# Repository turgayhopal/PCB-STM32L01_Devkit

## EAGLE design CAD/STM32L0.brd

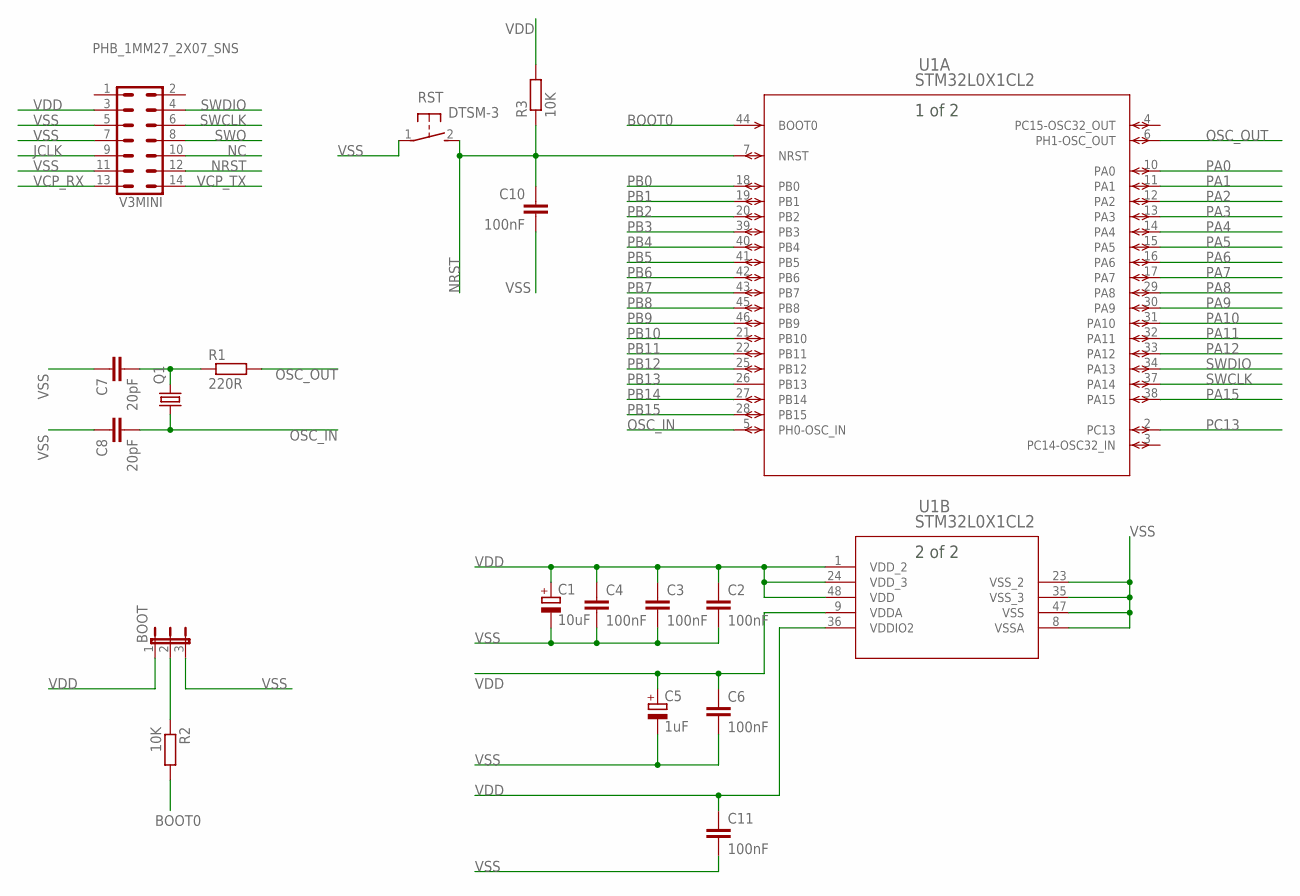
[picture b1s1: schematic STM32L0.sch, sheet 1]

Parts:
BOOT: JP2E; JP2
C1: 10uF; SMC_A
C2, C3, C4, C6, C10, C11: 100nF; C0805
C5: 1uF; SMC_A
C7, C8: 20pF; C0805
Q1: CRYSTALSM49; SM49
R1: 220R; R0805
R2, R3: 10K; R0805
RST: DTSM-3
U1: STM32L0X1CL2; LQFP48-7X7MM
V3MINI: PHB_1MM27_2X07_SNS

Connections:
BOOT0: R2.2, U1.44 (BOOT0)
JCLK: V3MINI.9
unnamed: C7.2, Q1.2, R1.1
unnamed: BOOT.2, R2.1
NC: V3MINI.10
NRST: C10.1, R3.1, RST.2, U1.7 (NRST), V3MINI.12
OSC_IN: C8.2, Q1.1, U1.5 (PH0-OSC_IN)
OSC_OUT: R1.2, U1.6 (PH1-OSC_OUT)
PA0: U1.10 (PA0); also elsewhere on the board
PA1: U1.11 (PA1); also elsewhere on the board
PA2: U1.12 (PA2); also elsewhere on the board
PA3: U1.13 (PA3); also elsewhere on the board
PA4: U1.14 (PA4); also elsewhere on the board
PA5: U1.15 (PA5); also elsewhere on the board
PA6: U1.16 (PA6); also elsewhere on the board
PA7: U1.17 (PA7); also elsewhere on the board
PA8: U1.29 (PA8); also elsewhere on the board
PA9: U1.30 (PA9); also elsewhere on the board
PA10: U1.31 (PA10); also elsewhere on the board
PA11: U1.32 (PA11); also elsewhere on the board
PA12: U1.33 (PA12); also elsewhere on the board
PA15: U1.38 (PA15); also elsewhere on the board
PB0: U1.18 (PB0); also elsewhere on the board
PB1: U1.19 (PB1); also elsewhere on the board
PB2: U1.20 (PB2); also elsewhere on the board
PB3: U1.39 (PB3); also elsewhere on the board
PB4: U1.40 (PB4); also elsewhere on the board
PB5: U1.41 (PB5); also elsewhere on the board
PB6: U1.42 (PB6); also elsewhere on the board
PB7: U1.43 (PB7); also elsewhere on the board
PB8: U1.45 (PB8); also elsewhere on the board
PB9: U1.46 (PB9); also elsewhere on the board
PB10: U1.21 (PB10); also elsewhere on the board
PB11: U1.22 (PB11); also elsewhere on the board
PB12: U1.25 (PB12); also elsewhere on the board
PB13: U1.26 (PB13); also elsewhere on the board
PB14: U1.27 (PB14); also elsewhere on the board
PB15: U1.28 (PB15); also elsewhere on the board
PC13: U1.2 (PC13); also elsewhere on the board
SWCLK: U1.37 (PA14), V3MINI.6
SWDIO: U1.34 (PA13), V3MINI.4
SWO: V3MINI.8
VCP_RX: V3MINI.13
VCP_TX: V3MINI.14
VDD: BOOT.1, C1.+, C2.1, C3.1, C4.1, C5.+, C6.1, C11.1, R3.2, U1.1 (VDD_2), U1.9 (VDDA), U1.24 (VDD_3), U1.36 (VDDIO2), U1.48 (VDD), V3MINI.3; also elsewhere on the board
VSS: BOOT.3, C1.-, C2.2, C3.2, C4.2, C5.-, C6.2, C7.1, C8.1, C10.2, C11.2, RST.1, U1.8 (VSSA), U1.23 (VSS_2), U1.35 (VSS_3), U1.47 (VSS), V3MINI.5, V3MINI.7, V3MINI.11; also elsewhere on the board

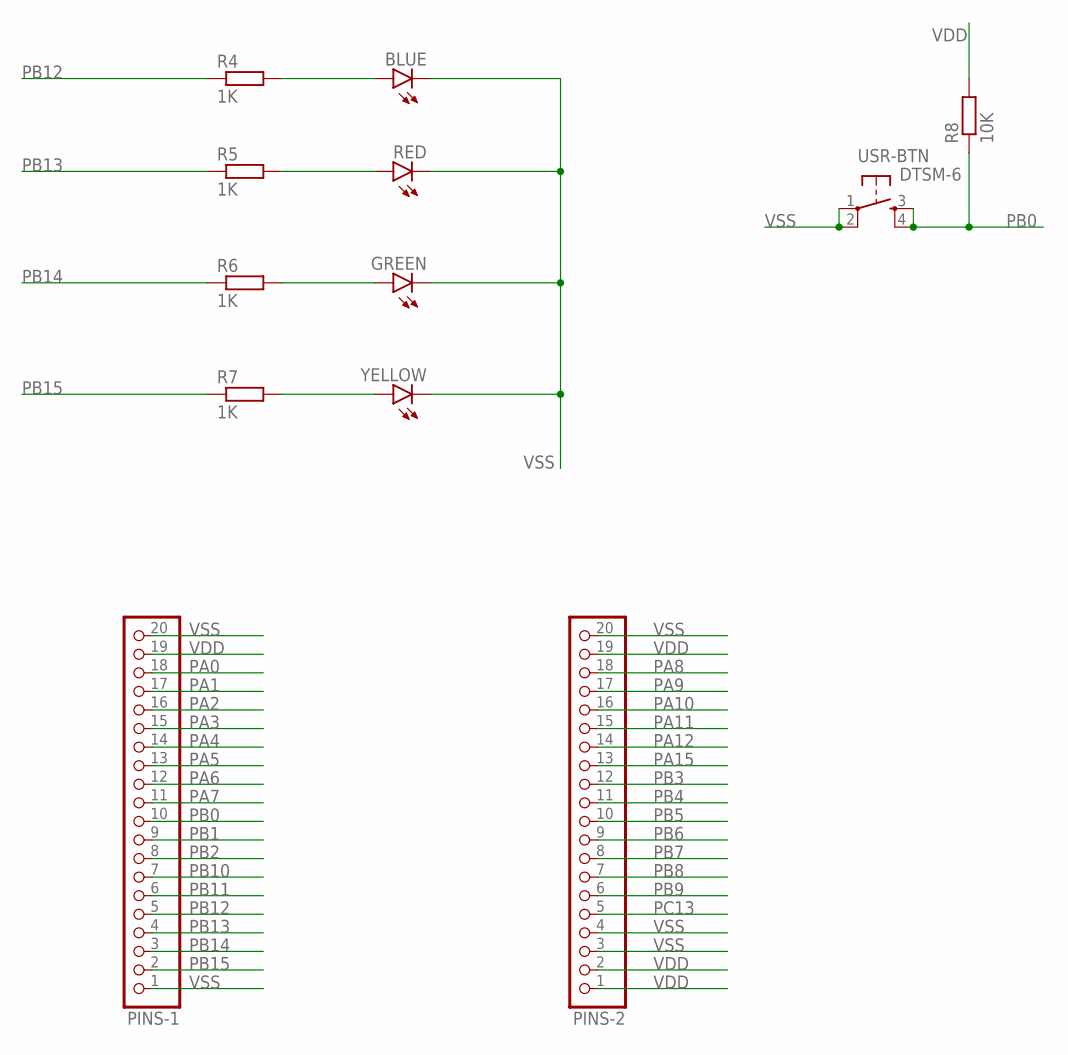
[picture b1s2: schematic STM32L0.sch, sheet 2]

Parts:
BLUE: LEDCHIPLED_0805; CHIPLED_0805
GREEN: LEDCHIPLED_0805; CHIPLED_0805
PINS-1, PINS-2: PINHD-1X20; 1X20
R4, R5, R6, R7: 1K; R0805
R8: 10K; R0805
RED: LEDCHIPLED_0805; CHIPLED_0805
USR-BTN: DTSM-6
YELLOW: LEDCHIPLED_0805; CHIPLED_0805

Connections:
unnamed: BLUE.A, R4.2
unnamed: R5.2, RED.A
unnamed: GREEN.A, R6.2
unnamed: R7.2, YELLOW.A
PA0: PINS-1.18; also elsewhere on the board
PA1: PINS-1.17; also elsewhere on the board
PA2: PINS-1.16; also elsewhere on the board
PA3: PINS-1.15; also elsewhere on the board
PA4: PINS-1.14; also elsewhere on the board
PA5: PINS-1.13; also elsewhere on the board
PA6: PINS-1.12; also elsewhere on the board
PA7: PINS-1.11; also elsewhere on the board
PA8: PINS-2.18; also elsewhere on the board
PA9: PINS-2.17; also elsewhere on the board
PA10: PINS-2.16; also elsewhere on the board
PA11: PINS-2.15; also elsewhere on the board
PA12: PINS-2.14; also elsewhere on the board
PA15: PINS-2.13; also elsewhere on the board
PB0: PINS-1.10, R8.1, USR-BTN.3, USR-BTN.4; also elsewhere on the board
PB1: PINS-1.9; also elsewhere on the board
PB2: PINS-1.8; also elsewhere on the board
PB3: PINS-2.12; also elsewhere on the board
PB4: PINS-2.11; also elsewhere on the board
PB5: PINS-2.10; also elsewhere on the board
PB6: PINS-2.9; also elsewhere on the board
PB7: PINS-2.8; also elsewhere on the board
PB8: PINS-2.7; also elsewhere on the board
PB9: PINS-2.6; also elsewhere on the board
PB10: PINS-1.7; also elsewhere on the board
PB11: PINS-1.6; also elsewhere on the board
PB12: PINS-1.5, R4.1; also elsewhere on the board
PB13: PINS-1.4, R5.1; also elsewhere on the board
PB14: PINS-1.3, R6.1; also elsewhere on the board
PB15: PINS-1.2, R7.1; also elsewhere on the board
PC13: PINS-2.5; also elsewhere on the board
VDD: PINS-1.19, PINS-2.1, PINS-2.2, PINS-2.19, R8.2; also elsewhere on the board
VSS: BLUE.C, GREEN.C, PINS-1.1, PINS-1.20, PINS-2.3, PINS-2.4, PINS-2.20, RED.C, USR-BTN.1, USR-BTN.2, YELLOW.C; also elsewhere on the board

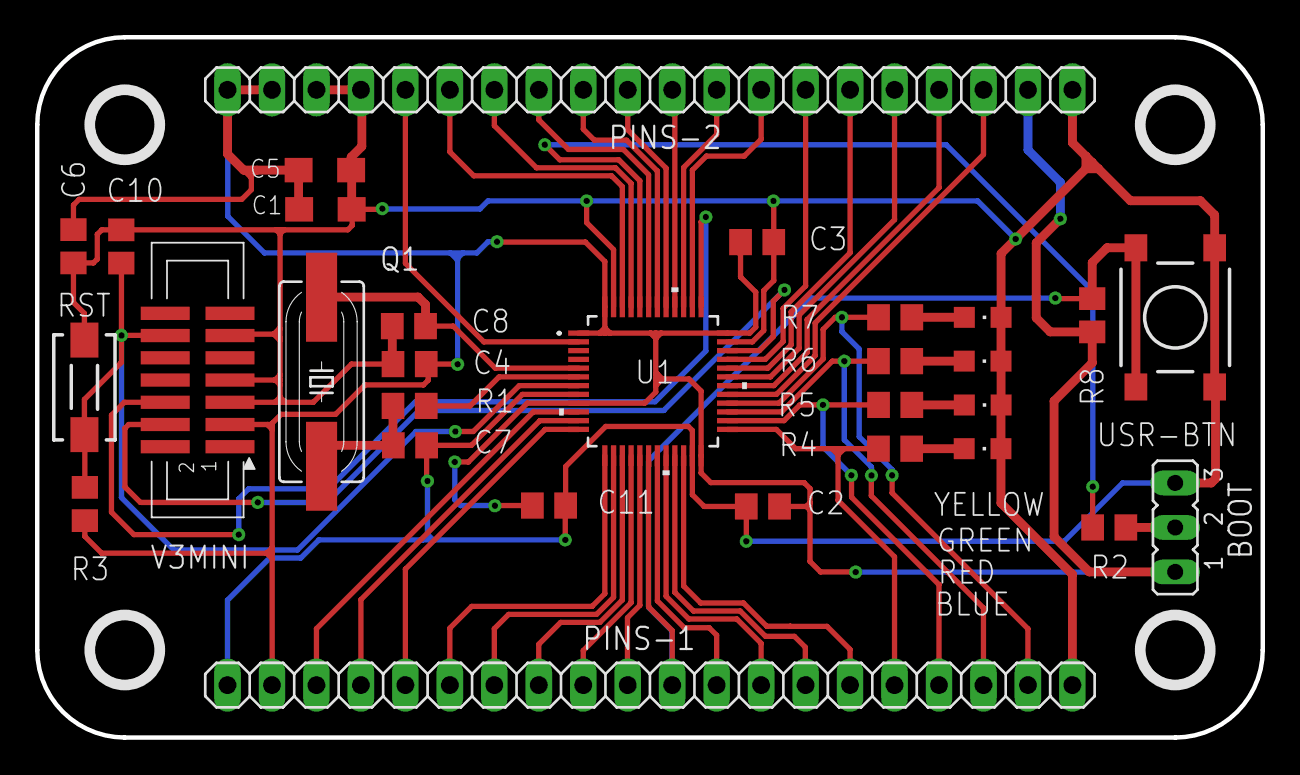
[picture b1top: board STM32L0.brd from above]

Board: 2 copper layers, 70.0 x 40.0 mm, 30 parts (0 on the bottom side), 45 nets.

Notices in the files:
parts and their libraries:
COPYRIGHT: Copyright (C) 2016 Accelerated Designs. All rights reserved
